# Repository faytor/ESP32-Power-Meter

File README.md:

# Smart AC Power Meter based on ESP32-C3 module
***

> **⚠ WARNING: Project still in progress.**  
> This project is still under development. However, I have successfully tested the following features: 
***
- Flashing and debugging the ESP32 module via USB-C ✅
- Blink the LED on GPIO pin 0 ✅
- I2C communication with the ACS37800 IC (read and write registers) ✅
- Fixed a schematic/hardware bug in the power switch logic (not shown in the image below) ✅
***

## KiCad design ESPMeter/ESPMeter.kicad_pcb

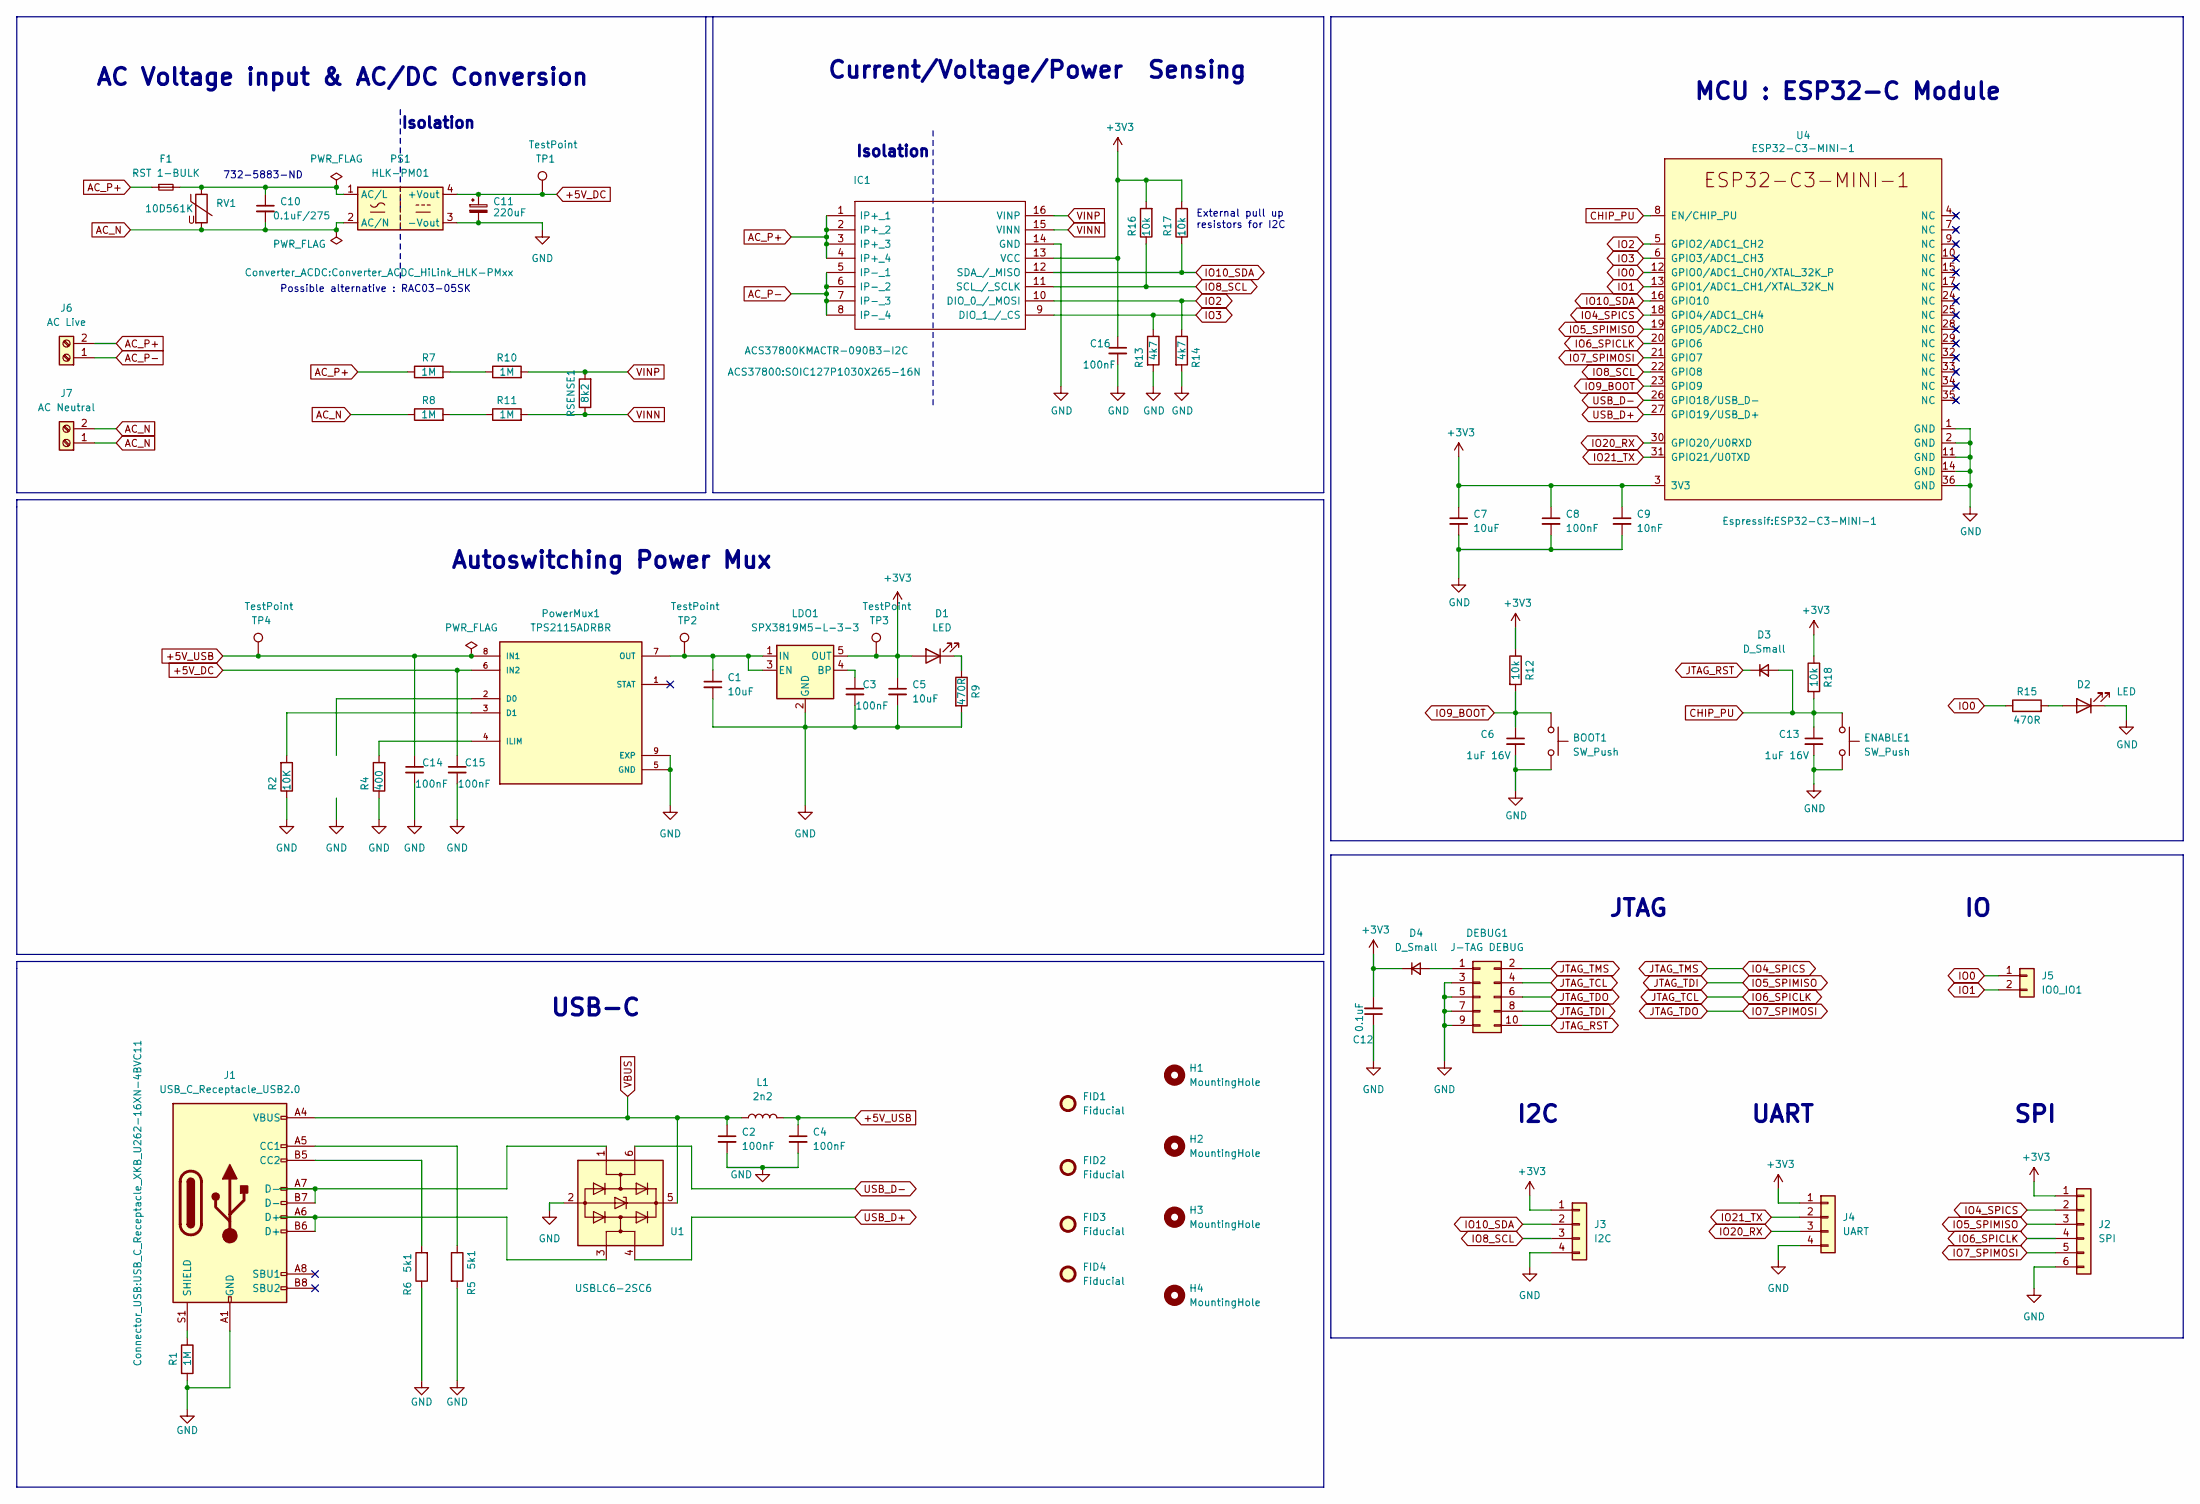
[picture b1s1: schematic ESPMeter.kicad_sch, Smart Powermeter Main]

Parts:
BOOT1: SW_Push; SW_PUSH_6mm_H4.3mm
C1, C5, C7: 10uF; C_0805_2012Metric_Pad1.18x1.45mm_HandSolder
C2, C3, C4, C8, C14, C15, C16: 100nF; C_0805_2012Metric_Pad1.18x1.45mm_HandSolder
C6, C13: 1uF 16V; C_0805_2012Metric_Pad1.18x1.45mm_HandSolder; LCSC C52923
C9: 10nF; C_0805_2012Metric_Pad1.18x1.45mm_HandSolder
C10: 0.1uF/275; C_Rect_L13.0mm_W8.0mm_P10.00mm_FKS3_FKP3_MKS4
C11: 220uF; CP_Radial_D10.0mm_P5.00mm
C12: 0.1uF; C_0805_2012Metric_Pad1.18x1.45mm_HandSolder
D1: LED; LED_0805_2012Metric_Pad1.15x1.40mm_HandSolder
D2: LED; LED_0805_2012Metric_Pad1.15x1.40mm_HandSolder; LCSC C2286
D3, D4: D_Small; D_0805_2012Metric_Pad1.15x1.40mm_HandSolder
DEBUG1: J-TAG DEBUG; PinHeader_2x05_P1.27mm_Vertical
ENABLE1: SW_Push; SW_PUSH_6mm_H4.3mm
F1: RST 1-BULK; FUSE_RST-1-BULK
FID1, FID2, FID3, FID4: Fiducial; Fiducial_0.5mm_Mask1.5mm
H1, H2, H3, H4: MountingHole; MountingHole_3.2mm_M3_Pad_TopBottom
IC1: ACS37800KMACTR-090B3-I2C; SOIC127P1030X265-16N; Manufacturer_Part_Number ACS37800KMACTR-090B3-I2C
J1: USB_C_Receptacle_USB2.0; USB_C_Receptacle_XKB_U262-16XN-4BVC11
J2: SPI; PinHeader_1x06_P2.54mm_Vertical
J3: I2C; PinHeader_1x04_P2.54mm_Vertical
J4: UART; PinHeader_1x04_P2.54mm_Vertical
J5: IO0_IO1; PinHeader_1x02_P2.54mm_Vertical
J6: AC Live; TerminalBlock_Phoenix_MKDS-3-2-5.08_1x02_P5.08mm_Horizontal
J7: AC Neutral; TerminalBlock_Phoenix_MKDS-3-2-5.08_1x02_P5.08mm_Horizontal
L1: 2n2; L_0805_2012Metric_Pad1.15x1.40mm_HandSolder
LDO1: SPX3819M5-L-3-3; SOT-23-5
PS1: HLK-PM01; Converter_ACDC_HiLink_HLK-PMxx
PowerMux1: TPS2115ADRBR; SON65P300X300X100-9N
R1: 1M; R_0805_2012Metric_Pad1.20x1.40mm_HandSolder
R2: 10K; R_0805_2012Metric_Pad1.20x1.40mm_HandSolder
R4: 400; R_0805_2012Metric_Pad1.20x1.40mm_HandSolder
R5, R6: 5k1; R_0805_2012Metric_Pad1.20x1.40mm_HandSolder
R7, R8, R10, R11: 1M; R_1206_3216Metric_Pad1.30x1.75mm_HandSolder
R9, R15: 470R; R_0805_2012Metric_Pad1.20x1.40mm_HandSolder
R12, R16, R17, R18: 10k; R_0805_2012Metric_Pad1.20x1.40mm_HandSolder
R13, R14: 4k7; R_0805_2012Metric_Pad1.20x1.40mm_HandSolder
RSENSE1: 8k2; R_0805_2012Metric_Pad1.20x1.40mm_HandSolder
RV1: 10D561K; RV_Disc_D9mm_W3.5mm_P5mm
TP1, TP2, TP3, TP4: TestPoint; TestPoint_THTPad_2.0x2.0mm_Drill1.0mm
U1: USBLC6-2SC6; SOT-23-6_Handsoldering
U4: ESP32-C3-MINI-1; LCSC C2838502

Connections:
+3V3: C5.1, C7.1, C8.1, C9.1, C12.2, C16.1, D1.2 (A), D4.1 (K), IC1.13 (VCC), J2.1, J3.1, J4.1, LDO1.5 (OUT), R12.1, R16.2, R17.2, R18.1, TP3.1, U4.3 (3V3)
+5V_DC: C11.1, C15.1, PS1.4 (+Vout), PowerMux1.6 (IN2), TP1.1
AC_N: C10.2, J7.1, J7.2, PS1.2 (AC/N), R8.1, RV1.2
AC_P+: F1.1, IC1.1 (IP+_1), IC1.2 (IP+_2), IC1.3 (IP+_3), IC1.4 (IP+_4), J6.2, R7.1
AC_P-: IC1.5 (IP-_1), IC1.6 (IP-_2), IC1.7 (IP-_3), IC1.8 (IP-_4), J6.1
CHIP_PU: C13.1, D3.2 (A), ENABLE1.1, R18.2, U4.8 (EN/CHIP_PU)
GND: BOOT1.2, C1.2, C2.2, C3.2, C4.2, C5.2, C6.2, C7.2, C8.2, C9.2, C11.2, C12.1, C13.2, C14.2, C15.2, C16.2, D2.1 (K), DEBUG1.3, DEBUG1.5, DEBUG1.7, DEBUG1.9, ENABLE1.2, IC1.14 (GND), J1.A1 (GND), J1.A12 (GND), J1.B1 (GND), J1.B12 (GND), J2.6, J3.4, J4.4, LDO1.2 (GND), PS1.3 (-Vout), PowerMux1.5 (GND), PowerMux1.9 (EXP), R1.2, R2.1, R4.1, R5.2, R6.1, R9.2, R13.2, R14.2, U1.2 (GND), U4.1 (GND), U4.2 (GND), U4.11 (GND), U4.14 (GND), U4.36 (GND); also elsewhere on the board
IO0: J5.1, R15.1, U4.12 (GPIO0/ADC1_CH0/XTAL_32K_P)
IO1: J5.2, U4.13 (GPIO1/ADC1_CH1/XTAL_32K_N)
IO2: IC1.10 (DIO_0_/_MOSI), R14.1, U4.5 (GPIO2/ADC1_CH2)
IO3: IC1.9 (DIO_1_/_CS), R13.1, U4.6 (GPIO3/ADC1_CH3)
IO4_SPICS: DEBUG1.2, J2.2, U4.18 (GPIO4/ADC1_CH4)
IO5_SPIMISO: DEBUG1.8, J2.3, U4.19 (GPIO5/ADC2_CH0)
IO6_SPICLK: DEBUG1.4, J2.4, U4.20 (GPIO6)
IO7_SPIMOSI: DEBUG1.6, J2.5, U4.21 (GPIO7)
IO8_SCL: IC1.11 (SCL_/_SCLK), J3.3, R16.1, U4.22 (GPIO8)
IO9_BOOT: BOOT1.1, C6.1, R12.2, U4.23 (GPIO9)
IO10_SDA: IC1.12 (SDA_/_MISO), J3.2, R17.1, U4.16 (GPIO10)
IO20_RX: J4.3, U4.30 (GPIO20/U0RXD)
IO21_TX: J4.2, U4.31 (GPIO21/U0TXD)
JTAG_RST: D3.1 (K), DEBUG1.10
unnamed: C10.1, F1.2, PS1.1 (AC/L), RV1.1
unnamed: D1.1 (K), R9.1
unnamed: D2.2 (A), R15.2
unnamed: D4.2 (A), DEBUG1.1
unnamed: J1.A5 (CC1), R5.1
unnamed: J1.B5 (CC2), R6.2
unnamed: J1.A6 (D+), J1.B6 (D+), U1.3 (I/O2)
unnamed: J1.A7 (D-), J1.B7 (D-), U1.1 (I/O1)
unnamed: J1.S1 (SHIELD), R1.1
unnamed: C3.1, LDO1.4 (BP)
unnamed: C1.1, LDO1.1 (IN), LDO1.3 (EN), PowerMux1.7 (OUT), TP2.1
unnamed 32: PowerMux1.2 (D0); also elsewhere on the board
unnamed: PowerMux1.4 (ILIM), R4.2
unnamed: R7.2, R10.1
unnamed: R8.2, R11.1
USB_D+: U1.4 (I/O2), U4.27 (GPIO19/USB_D+)
USB_D-: U1.6 (I/O1), U4.26 (GPIO18/USB_D-)
VBUS: C2.1, J1.A4 (VBUS), J1.A9 (VBUS), J1.B4 (VBUS), J1.B9 (VBUS), L1.1, U1.5 (VBUS)
VINN: IC1.15 (VINN), R11.2, RSENSE1.1
VINP: IC1.16 (VINP), R10.2, RSENSE1.2

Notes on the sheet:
UART
External pull up resistors for I2C
SPI
AC Voltage input & AC/DC Conversion
JTAG
Current/Voltage/Power Sensing
I2C
Autoswitching Power Mux
Isolation
Possible alternative : RAC03-05SK
USB-C
MCU : ESP32-C Module
732-5883-ND

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
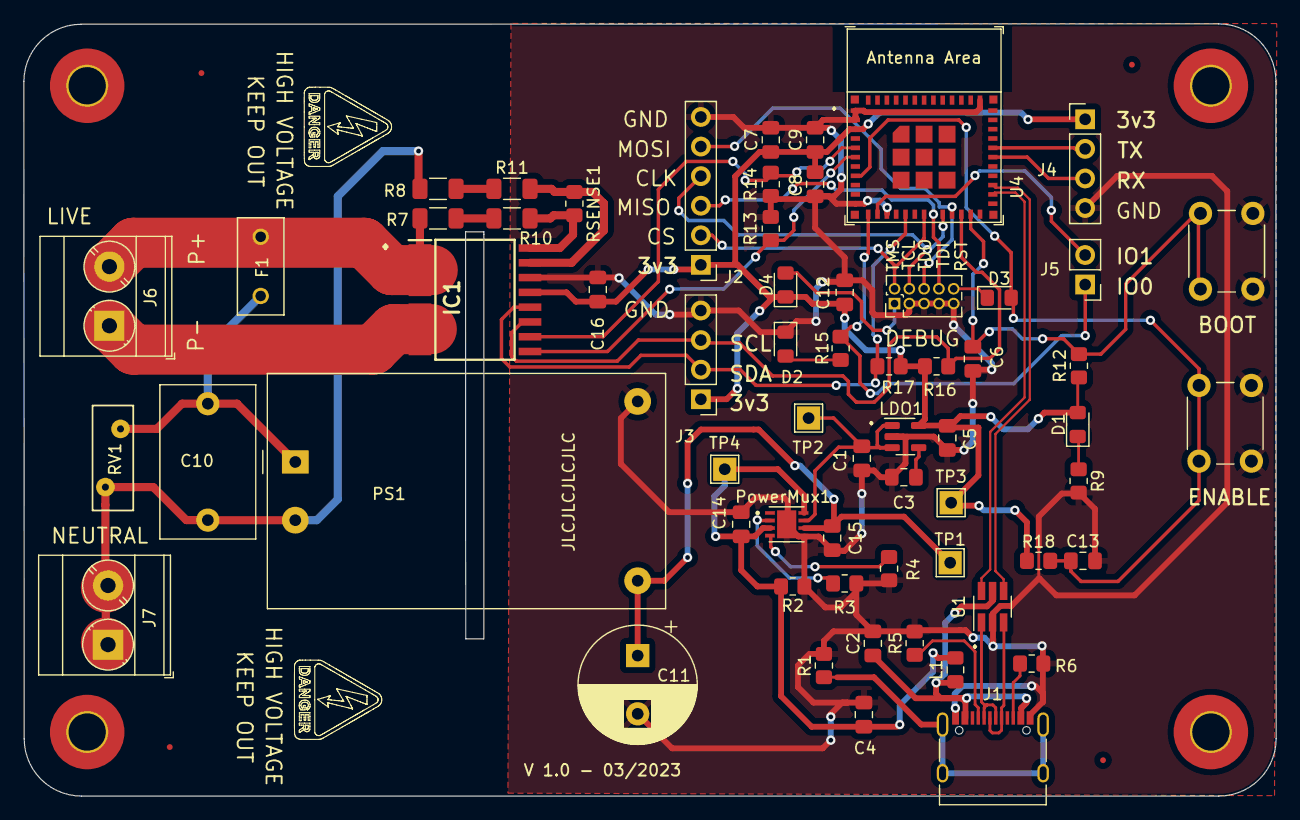
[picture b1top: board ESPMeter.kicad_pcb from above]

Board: 2 copper layers, 107.5 x 66.3 mm, 70 parts (0 on the bottom side), 42 nets.

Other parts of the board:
R3: 10k; R_0805_2012Metric_Pad1.20x1.40mm_HandSolder

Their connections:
GND: R3.1; also elsewhere on the board
unnamed 32: R3.2; also elsewhere on the board

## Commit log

2023-04-30 Add the Hardware parte
